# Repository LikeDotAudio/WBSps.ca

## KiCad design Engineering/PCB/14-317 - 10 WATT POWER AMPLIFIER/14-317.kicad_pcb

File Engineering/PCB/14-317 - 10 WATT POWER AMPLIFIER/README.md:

# 14-317 - 10 WATT POWER AMPLIFIER

**10 WATT POWER AMPLIFIER**

Converted to KiCad from `WBSps Engineering from H drive/WBSps - M7XX/M719/TANGO/14-317.PCB` (tango).

| Components | Pads | Track segments | Vias | Pours |
|---|---|---|---|---|
| 82 | 212 | 357 | 0 | 3 |

Nets: from `WBSps Engineering from H drive/WBSps - M7XX/M719/ORCAD/M719.NET`.

Other copies of the same file:

- `WBSps Engineering from H drive-20261018T013433Z-1-002/WBSps Engineering from H drive/WBSps - M7XX/M719/TANGO/14-317.PCB`

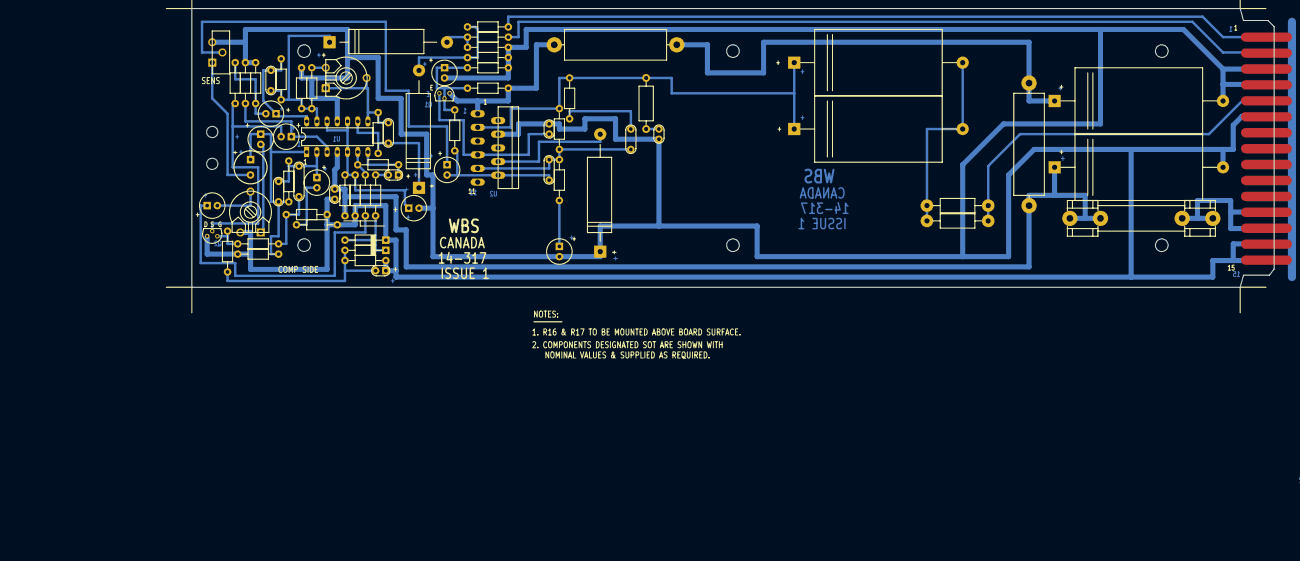
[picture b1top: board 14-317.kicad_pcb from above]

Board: 2 copper layers, 269.2 x 69.3 mm, 83 parts (0 on the bottom side), 44 nets.

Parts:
C10: 47/50; RAD.15
C14, C20: 10/50; RAD.1
C15, C28, C31, C32, C33, C34: 22/25; RAD.1
C16: 220P; CAP.2
C17, C38: 100/25; EC115
C18, C21, C24: 0.1/50; CAP.1
C19: 68P; CAP.2
C22, C23, C39, C40: 2200/35; EC165
C25: 100P; CAP.2
C26: 47/25; RAD.1
C27: 0.47; CAP.3
C29, C30: 2u2/35; TANTA.1
C35, C36: 22P; CAP.2
C37: SOT; EC115
D1, D2: 1N4148; DO-35
F1: AGC 1.5; AGC
H: (no value)
L1: 0.7UH; UNKNOWN
P1: EDGE15
Q1: 2N3904; TO-92
Q2: P1087E; TO-92
R9: 5K; PT10H
R10, R13, R21, R22, R30, R39, R42: 100K; R1/4
R11: 91K; R1/4
R12, R25: 22K; R1/4
R14, R26, R33, R34, R38: 4K7; R1/4
R15: 2R2 1/2W; R1/2
R16, R17: 2R2 1W; R01MF
R18: 75K; R1/4
R19, R37, R43: 15K; R1/4
R20: 470; R1/4
R23, R29, R32: 1M; R1/4
R24: 10K; R1/4
R27: 39K; R1/4
R28: 3K3; R1/4
R31: 5K; PT10V
R35: 2K; PT10V
R36: 4K3; R1/4
R40, R41: SOT; R1/4
R44, R45: 5R 5W; R05WE
TITLE1: TITLE
U1: LM837; DIP14
U2: LM2876T; XDIL11
W1, W2, W3, W5: 4-40SCREW
X1, X4: 4-40SCREW
X2: TITLEB

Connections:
GND: C15.2, C17.1, C18.2, C20.2, C21.2, C24.2, C29.1, C34.2, C39.2, C40.2, D1.1, P1.3, P1.4, P1.6, P1.14, P1.15, Q2.3, R9.3, R10.2, R20.2, R21.1, R22.2, R24.2, R29.2, R30.2, R31.3, R33.1, R39.2, R41.2, R42.2, U1.11, U2.4
N00001: C36.1, C38.1, R38.1, U1.9
N00002: C36.2, R35.1, R35.2, R38.2, U1.8
N00003: P1.1, R43.1
N00004: C38.2, R42.1, R43.2
N00005: R35.3, R36.1
N00006: C35.1, C37.1, R36.2, R37.1, R39.1, U1.13
N00007: C28.1, C35.2, R37.2, U1.14
N00008: Q1.3, R11.1, R44.1, U2.1
N00009: C40.1, R44.2, R45.1
N00010: P1.2, R40.1
N00011: C37.2, R40.2, R41.1
N00012: L1.2, P1.5, R16.2, R17.2
N00013: C15.1, Q1.2, R10.1, R11.2, R18.1
N00014: C14.2, C16.1, R18.2, U2.10
N00015: C22.2, C23.2, L1.1, R16.1, R17.1
N00016: C28.2, R24.1, R25.1
N00017: C33.2, Q2.2, R25.2
N00018: C33.1, R22.1, U1.3
N00019: C10.1, C25.2, C32.1, R19.2, R30.1, U1.1
N00020: C10.2, R9.1
N00021: C14.1, R9.2
N00022: C25.1, C26.1, C27.2, R19.1, U1.2
N00023: F1.1, P1.12, P1.13
N00024: C22.1, C23.1, R12.2, R13.2, R15.1, U2.3
N00025: C16.2, C19.1, R13.1, R14.1, U2.9
N00026: C18.1, Q1.1, U2.7
N00027: C17.2, U2.8
N00028: C27.1, R21.2, R23.2
N00029: Q2.1, R23.1, R32.1
N00030: C32.2, R31.1
N00031: C26.2, R20.1
N00032: C21.1, R15.2
N00033: C19.2, R12.1
N00034: C20.1, R14.2
N00035: C30.1, R27.1, U1.7
N00036: R26.1, R27.2, U1.6
N00037: C31.2, R31.2
N00038: C29.2, D2.2, R29.1, R32.2
N00039: C31.1, R26.2
N00040: D1.2, D2.1, R28.1
N00041: C30.2, R28.2
V/2: C34.1, R33.2, R34.1, U1.5, U1.10, U1.12
VCC: C24.1, C39.1, F1.2, R34.2, R45.2, U1.4

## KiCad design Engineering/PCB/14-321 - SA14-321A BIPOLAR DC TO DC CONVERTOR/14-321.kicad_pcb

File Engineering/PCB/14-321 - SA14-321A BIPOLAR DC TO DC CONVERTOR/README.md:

# 14-321 - SA14-321A BIPOLAR DC TO DC CONVERTOR

**SA14-321A BIPOLAR DC TO DC CONVERTOR**

Converted to KiCad from `WBSps Engineering from H drive/WBSps - SA14-XXX/SA14-321/TANGO/14-321.PCB` (tango).

| Components | Pads | Track segments | Vias | Pours |
|---|---|---|---|---|
| 41 | 88 | 1426 | 7 | 55 |

Nets: from `WBSps Engineering from H drive/WBSps - SA14-XXX/SA14-321/ORCADWIN/SA14321A.NET`.

Other copies of the same file:

- `WBSps Engineering from H drive-20261018T013433Z-1-002/WBSps Engineering from H drive/WBSps - SA14-XXX/SA14-321/TANGO/14-321.PCB`

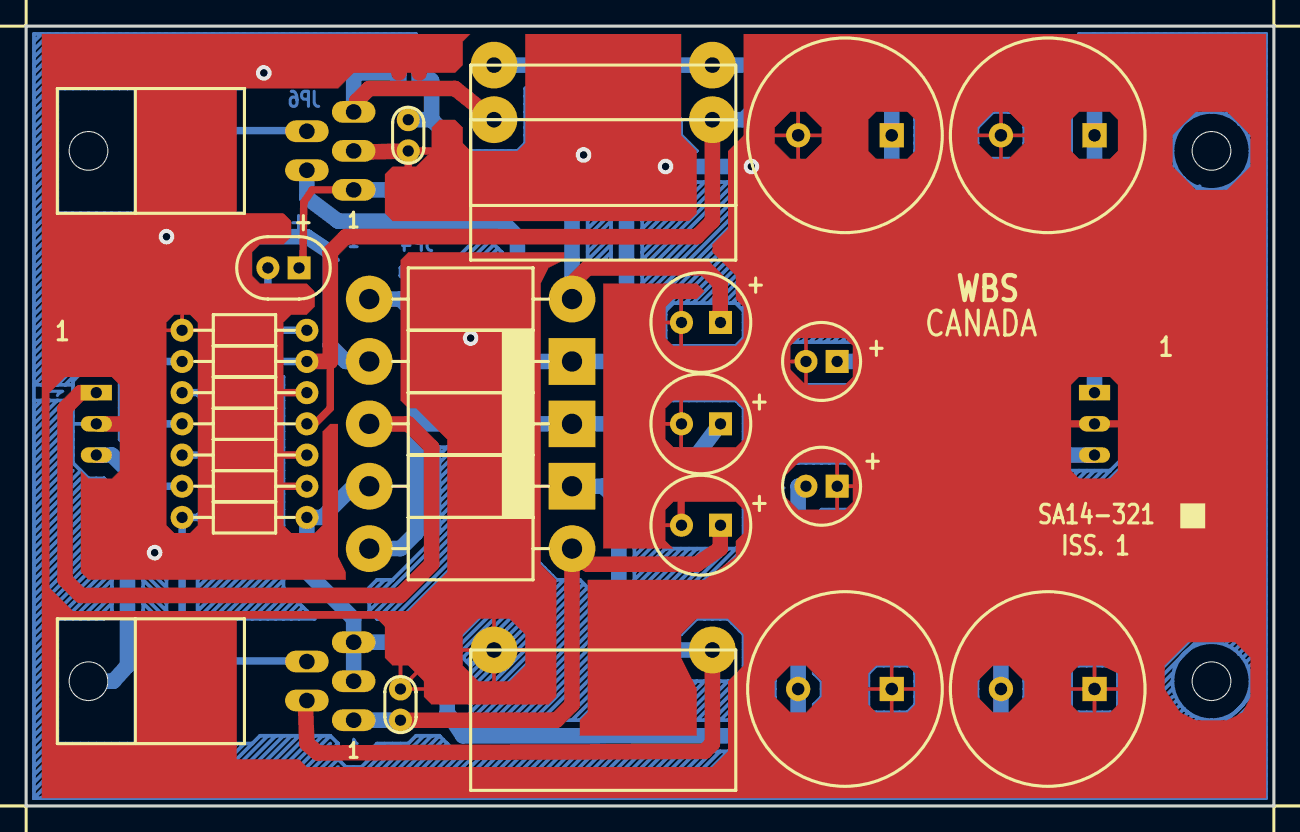
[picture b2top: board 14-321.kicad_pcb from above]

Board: 2 copper layers, 101.6 x 63.5 mm, 41 parts (0 on the bottom side), 11 nets.

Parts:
C1, C3: 0.1/50; CAP.1
C2: 4.7/35; TANTB.1
C4, C11: 2200/25; E1000R25
C5, C12: SOT; E1000R25
C6, C8, C10: 47/50; RAD.125
C7, C9: 27/35; RAD.1
CR1, CR2, CR3: 1N5822; 17-02
JP1, JP4, JP5, JP6: JUMPER; LINK2
JP2, JP3, JP7: JUMPER; LINK4
L1, L2, L3: 80-36; 80-36U
P1, P2: CON3; SIP3
R1: 620; R1/4
R2, R3: 22K; R1/4
R4, R5: 20K; R1/4
R6, R7: 931 1%; R1/4
R8, R9: 1R5 3W; R03WE
TITLE1A: TITLE
U1, U2: LM2575T-ADJ; T05A
X1, X2: 4-40SCREW

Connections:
GND POWER: C1.2, C3.2, C4.2, C6.2, C7.2, C8.2, C9.1, C10.2, C11.1, CR1.2, L3.2, P1.2, P2.2, R3.2, R5.2, R6.2, U1.3, U1.5
N00352: R3.1, R5.1, R7.1, U2.4
N01255: R2.1, R4.1, R6.1, U1.4
N03043: CR2.2, P1.1
N03135: C8.1, CR2.1, R8.1, R9.1
N03171: C3.1, C10.1, R9.2, U2.1
N03204: CR3.1, L3.1, U2.2
N03866: C1.1, C6.1, R8.2, U1.1
N04145: CR1.1, L1.1, U1.2
N04149: C4.1, C7.1, L1.2, P2.1, R2.2, R4.2
N04204: C9.2, C11.2, CR3.2, P2.3, R7.2, U2.3, U2.5

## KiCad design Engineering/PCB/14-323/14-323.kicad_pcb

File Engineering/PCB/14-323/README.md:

# 14-323

Converted to KiCad from `WBSps Engineering from H drive/WBSps - CONSOLES/REN TV Console/M926/OLD/14-323.PCB` (tango).

| Components | Pads | Track segments | Vias | Pours |
|---|---|---|---|---|
| 191 | 740 | 2946 | 118 | 17 |

Nets: from `WBSps Engineering from H drive/WBSps - CONSOLES/REN TV Console/M926/OLD/14-323_1.NET`.

Other copies of the same file:

- `wbsPS-NOT UPLOADED/XXX - REN TV Console-20221115T024141Z-001/REN TV Console/M926/OLD/14-323.PCB`
- `WBSps Engineering from H drive-20261018T013433Z-1-003/WBSps Engineering from H drive/WBSps - CONSOLES/REN TV Console/M926/OLD/14-323.PCB`

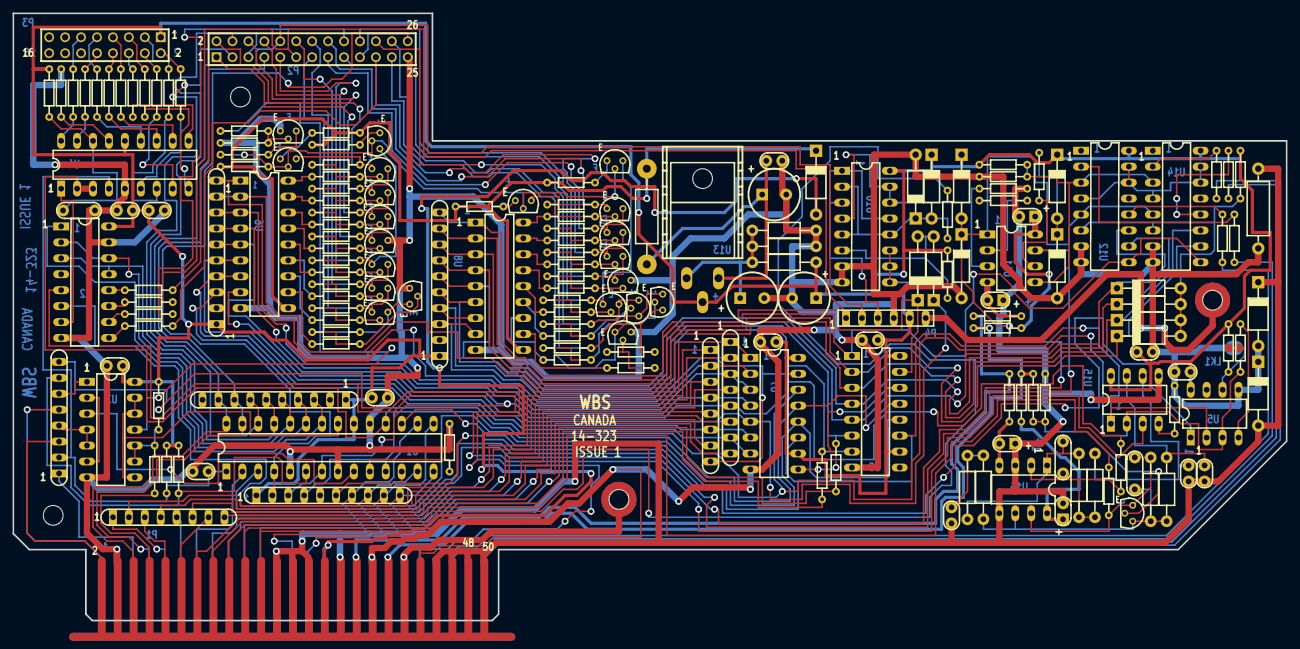
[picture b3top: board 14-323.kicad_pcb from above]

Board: 2 copper layers, 202.9 x 96.8 mm, 191 parts (0 on the bottom side), 196 nets.

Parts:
C1, C2, C3, C4, C5, C7, C8, C9, C13, C16, C18, C20, C21: 0.1; CAP.1
C6: 22P; CAP.2
C10, C11, C19, C22: 1/35; TANTA.1
C12, C14, C15: 47/50; RAD.15
C17: 0.33; CAP.2
C23: SOT; CAP.2
D1, D2, D3, D4, D5, D7, D8, D9, D10, D11, D12, D15: 1N4148; DO-35
D6, D13, D14: 1N4003; DO-43
LK1: LINK2
P1: EDGE50/100
P2: 929715-01-13; CONN26
P3: 929715-01-08; CONN16
P4: 65645-106; CONNECT6
Q1: 2N3904; TO-92
Q2, Q3, Q4, Q5, Q6, Q7, Q8, Q9, Q10, Q11, Q12, Q13, Q14, Q15, Q16, Q17, Q18, Q19, Q20, Q21, Q22: 2N3906; TO-92
R1, R4, R5, R12, R15, R76, R102: 100K; R1/8
R2, R8, R43, R44: 82; SIP8
R3, R6, R42, R63: 10K; SIP10
R7, R9, R10, R11: 100-1/8W-5%; R1/8
R13: 39K; R1/8
R14, R29, R30, R53, R54, R64, R65, R75: 100; R1/8
R16, R17, R19, R20, R21, R22, R24, R25, R26, R27: 220; R1/8
R18, R69, R73, R82, R83, R93: 10K; R1/8
R23: 4K7; R1/8
R28: 1K5; R1/8
R31, R32, R33, R34, R35, R36, R37, R38, R39, R40, R41, R45, R46, R47, R48, R49, R50, R51, R52, R55, R56, R57, R58, R59, R60, R61, R62, R66, R67, R68, R70, R71, R72: 10K-1/8W-5%; R1/8
R74, R79, R97, R103: 620; R1/8
R77, R89: 1K; R1/8
R78, R80, R91, R94, R98: 10; R1/8
R81: 30 1W; R01MF
R84, R85: SOT; R1/8
R86: 430; R1/4
R87: SOT; R1/4
R88: 1K3; R1/4
R90: 27 1/2W; R1/2
R92: 15K; R1/8
R95: 33K2 1%; R1/4
R96, R101, R104: 100K 1%; R1/4
R99, R100: 10K 1%; R1/4
R105: 150K; R1/8
U1: PIC16C73; SDIP28
U2: 74HC139; DIP16
U3: 74HC00N; DIP14
U4: PIC16C54RC/P; DIP18
U5: 93LC66; DIP8
U6, U8: ULN2803; DIP18
U7, U9: 74HC595; DIP16
U10, U12, U14: 74HC4053; DIP16
U11, U16: LF353; DIP8
U13: LM317; TO-220HS
U15: LT1451CN8; DIP8
W1: TITLE
X1, X2, X3, X4: 4-40SCREW

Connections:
+5V: C2.1, C3.1, C4.2, C5.1, C7.1, C8.1, C9.1, C15.1, C16.1, D1.CATHODE, D3.CATHODE, D9.CATHODE, P3.1, P4.5, R1.2, R3.1, R4.2, R6.1, R12.2, R13.2, R18.2, R42.1, R63.1, R82.2, R83.1, R84.1, R86.1, U1.20, U2.16, U3.14, U4.14, U5.8, U7.10, U7.16, U9.10, U9.16, U10.16, U12.16, U13.2, U14.16, U15.8
+12V: D6.CATHODE, R28.2, R29.2, R30.2, R53.2, R54.2, R81.2, U6.10, U8.10
+24V: P1.37, P1.38, R74.1, R92.1, R97.1
-24V: P1.33, P1.34, R79.2, R103.2
/AUTO: D5.CATHODE, R63.10, U8.1, U9.15, U10.9, U10.10, U10.11
/CHIP1: U2.5, U15.3
/CHIP2: U2.6, U7.12, U9.12
/CHIP3: U2.7, U4.1
/CHON: R3.3, R44.5, R105.1, U1.7, U6.8
/FADER: D7.CATHODE, R42.5, U6.6, U7.5
/G1: D8.CATHODE, R63.5, U8.6, U9.5, U12.11
/G2: D10.CATHODE, R63.6, U8.5, U9.4, U12.10
/G3: D12.CATHODE, R63.7, U8.4, U9.3, U14.11
/G4: D15.CATHODE, R63.8, U8.3, U9.2, U14.10
/MSTR: R63.9, U8.2, U9.1, U12.9, U14.9
/OKAY: R3.4, U1.11, U7.13, U9.13
/PFAIL: R36.1, U3.11
/RST: C1.1, R1.1, R2.2, U1.1, U4.4
A0: D3.ANODE, D4.CATHODE, R77.2, U1.2, U11.1, U12.5, U14.5
A1: D9.ANODE, D11.CATHODE, R89.2, U1.3, U11.7
AUDIO COMMON: C10.2, C11.1, C18.2, C19.2, C20.2, C21.2, C22.1, D13.CATHODE, D14.ANODE, P1.23, P1.24, P1.26, P1.28, P1.31, P1.32, P1.44, P1.46, P1.48, P1.50, R76.2, R90.1, R93.2, U15.5, U16.3, U16.5
BASE: Q1.BASE, Q2.BASE, Q12.BASE, Q13.BASE, R28.1, R31.2
CHASSIS: P1.39, P1.40, P4.6
CTL COMMON: C1.2, C2.2, C3.2, C4.1, C5.2, C6.1, C7.2, C8.2, C9.2, C12.2, C13.2, C14.2, C15.2, C16.2, D2.ANODE, D4.ANODE, D11.ANODE, D13.ANODE, D14.CATHODE, LK1.1, LK1.2, P1.3, P1.4, P1.35, P1.36, P1.42, P2.25, P4.4, Q6.COLLECTOR, Q7.EMITTER, Q11.COLLECTOR, Q17.COLLECTOR, Q21.COLLECTOR, R5.1, R15.1, R18.1, R41.1, R85.2, R87.1, R88.1, R90.2, R102.1, U1.5, U1.8, U1.19, U2.8, U2.15, U3.7, U4.5, U5.5, U5.6, U6.9, U7.8, U8.9, U9.8, U10.7, U10.8, U12.7, U12.8, U14.7, U14.8
EECS: R3.6, U1.12, U5.1
N06346: U3.2, U3.6
N06588: R71.1, U8.13
N06609: R62.1, U8.15
N06615: R73.1, U8.11
N06641: R70.1, U8.14
N06647: R60.1, U8.17
N06654: R72.1, U8.12
N06672: R59.1, U8.18
N06674: R61.1, U8.16
N06862: R40.1, U6.15
N06864: R37.1, U6.18
N06884: R51.1, U6.12
N06894: R49.1, U6.14
N06899: R38.1, U6.17
N06914: R52.1, U6.11
N06951: R39.1, U6.16
N06955: R50.1, U6.13
N20977: U1.9, U3.3
N21031: R5.2, U1.10
N23877: R3.8, R8.4, U1.13
N27473: R63.4, R64.2, U8.7, U9.6
N27482: R63.3, R65.2, U8.8, U9.7
N31936: C23.1, R99.1, R104.2, U16.1
N31951: U12.4, U12.14, U12.15, U14.4, U14.14, U14.15
N31954: C21.1, R99.2, R100.1
N31985: C20.1, R101.1, U15.6
N31987: C23.2, R101.2, R104.1, R105.2, U16.2
N32012: C18.1, R95.1, U15.7
N32024: R80.2, U12.2
N32033: R78.2, U12.12
N32045: R102.2, U15.4
N32369: D1.ANODE, D2.CATHODE, R75.2, U10.2, U10.5, U10.12
N32380: D8.ANODE, D10.ANODE, D12.ANODE, D15.ANODE, R83.2, U12.6, U14.6
N32557: P2.5, R6.7, U1.26
N32570: P2.3, R6.6, U1.25
N32761: P1.7, P2.7, R6.8, U1.27
N32819: P1.21, R64.1
N32820: P1.22, R65.1
N32895: D6.ANODE, P1.29, P1.30
N32920: P1.25, R98.2
N32932: P1.27, R75.1
N34496: R76.1, U10.4, U10.14, U10.15, U11.3
N34497: R77.1, U11.2
N34507: R84.2, R85.1, U11.5, U12.3, U14.3
N34510: R89.1, U11.6
N35727: Q14.BASE, R55.2, R59.2
N35728: P2.16, Q12.COLLECTOR, Q14.EMITTER, R55.1
N35741: P2.15, Q14.COLLECTOR, Q15.EMITTER, R56.1
N35743: Q15.BASE, R56.2, R60.2
N35754: P2.17, Q15.COLLECTOR, Q16.EMITTER, R57.1
N35759: Q16.BASE, R57.2, R61.2
N35770: Q17.BASE, R58.2, R62.2
N35773: P2.20, Q16.COLLECTOR, Q17.EMITTER, R58.1
N35864: Q21.BASE, R69.2, R73.2
N35876: P2.23, Q20.COLLECTOR, Q21.EMITTER, R69.1
N35881: Q20.BASE, R68.2, R72.2
N35891: P2.24, Q19.COLLECTOR, Q20.EMITTER, R68.1
N35895: Q19.BASE, R67.2, R71.2
N35905: Q18.BASE, R66.2, R70.2
N35906: P2.19, Q13.COLLECTOR, Q18.EMITTER, R66.1
N35907: P2.22, Q18.COLLECTOR, Q19.EMITTER, R67.1
N35994: Q7.COLLECTOR, R31.1
N35998: Q7.BASE, R36.2, R41.2
N36007: P2.2, Q1.COLLECTOR, Q3.EMITTER, R32.1
N36010: Q3.BASE, R32.2, R37.2
N36024: P2.1, Q3.COLLECTOR, Q4.EMITTER, R33.1
N36026: Q4.BASE, R33.2, R38.2
N36036: P2.6, Q4.COLLECTOR, Q5.EMITTER, R34.1
N36040: Q5.BASE, R34.2, R39.2
N36051: Q6.BASE, R35.2, R40.2
N36057: P2.8, Q5.COLLECTOR, Q6.EMITTER, R35.1
N36111: Q11.BASE, R48.2, R52.2
N36127: Q10.BASE, R47.2, R51.2
N36129: P2.13, Q10.COLLECTOR, Q11.EMITTER, R48.1
N36144: Q9.BASE, R46.2, R50.2
N36146: P2.14, Q9.COLLECTOR, Q10.EMITTER, R47.1
N36158: Q8.BASE, R45.2, R49.2
N36159: P2.9, Q2.COLLECTOR, Q8.EMITTER, R45.1
N36161: P2.12, Q8.COLLECTOR, Q9.EMITTER, R46.1
N36173: C17.2, Q22.COLLECTOR, R95.2, R96.1, R100.2, U16.6
N36174: Q22.BASE, R92.2, R93.1
N36175: C17.1, Q22.EMITTER, R96.2, R98.1, U16.7
N36766: R2.7, R4.1, U1.6
N36828: R42.3, R44.7, U7.7
N36829: P1.20, R44.8
N36850: P1.19, R43.7
N36852: R42.10, R43.8, U6.1, U7.15
N36866: R42.9, R44.1, U6.2, U7.1
N36869: P1.14, R44.2
N36874: R42.8, R43.2, U6.3, U7.2
N36875: P1.13, R43.1
N36890: R42.7, R44.3, U6.4, U7.3
N36893: P1.16, R44.4
N36963: P1.17, R43.5
N36964: R42.4, R43.6, U6.7, U7.6
N37705: P2.26, R3.2, U1.4
N37729: P1.41, R2.8
N37739: P1.5, R2.1
N37747: P1.10, R8.3
N38081: R22.2, U4.10
N38087: R24.2, U4.9
N38089: R15.2, U4.15
N38092: R21.2, U4.11
N38095: R16.2, U4.18
N38098: R25.2, U4.8
N38112: R20.2, U4.12
N38113: R19.2, U4.13
N38118: R26.2, U4.7
N38119: R27.2, U4.6
N38134: P3.8, R20.1
N38135: P3.4, R25.1
N38140: P3.11, R16.1
N38142: P3.10, R17.1
N38143: P3.9, R19.1
N38144: P3.5, R24.1
N38145: P3.3, R26.1
N38147: P3.6, R22.1
N38148: P3.2, R27.1
N38149: P3.7, R21.1
N38334: R23.1, U5.4
N38376: R17.2, U4.17
N38383: C6.2, R13.1, U4.16
N38389: P1.6, P2.10, P4.2, R6.9, U1.28
N38660: R3.7, R8.2, U1.16
N38663: R3.9, R8.6, U1.15
N38666: P1.12, R8.7
N38667: P1.9, R8.1
N38668: P1.11, R8.5
N38774: R12.1, R14.1, U3.9, U3.10
N38790: P1.8, R14.2
N38803: U1.21, U3.8, U3.12, U3.13
N38818: R2.6, U3.1
N38819: R2.4, U3.4, U3.5
N38836: R3.10, R8.8, U1.14
N38908: R6.5, U1.24, U2.3, U2.13
N38911: R6.4, U1.23, U2.2, U2.14
N38922: R6.3, U1.22, U2.1
N39058: R7.2, U2.12
N39060: P2.4, R7.1
N39085: R9.2, U2.11
N39088: P2.11, P4.1, R9.1
N39096: R11.2, U2.9
N39101: R10.2, U2.10
N39105: P2.18, R10.1
N39107: P2.21, R11.1
N39205: P1.1, R2.5
N39207: P1.2, R2.3
N39227: P1.15, R43.3
N39231: R42.6, R43.4, U6.5, U7.4
N39290: P1.18, R44.6
N39307: Q1.EMITTER, R30.1
N39311: Q2.EMITTER, R29.1
N39383: Q12.EMITTER, R54.1
N39393: Q13.EMITTER, R53.1
N40214: C10.1, R74.2, U11.8
N40234: C11.2, R79.1, U11.4
N40241: C19.1, R97.2, U16.8
N40248: C22.2, R103.1, U16.4
N40361: D5.ANODE, D7.ANODE, R82.1, U10.6
N40410: P4.3, U10.1, U10.3, U10.13
N40497: P1.43, R78.1
N40500: P1.45, R80.1
N40517: R91.2, U14.12
N40518: R94.2, U14.2
N40523: P1.47, R91.1
N40525: P1.49, R94.1
N40795: C14.1, R86.2, R87.2, R88.2, U13.1
N41294: C12.1, C13.1, R81.1, U13.3
RIPPLE: U7.9, U9.14
SCLK: U1.17, U5.2, U7.11, U9.11, U15.1
SDATA: R23.2, U1.18, U4.2, U4.3, U5.3, U7.14, U15.2
